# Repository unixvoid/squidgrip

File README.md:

# Squidgrip

Squidgrip is a clamp-on USB-UART probe for programming ESP32 boards. It is a CP2102N on a small
USB-C board with a 6-pin pogo pin array on a thin tongue, plus a 3D printed clamp that presses that
tongue onto the programming pads of a target board.

It carries the ESP32 auto-reset circuit, so esptool, the ExpressLRS Configurator, PlatformIO, Arduino
IDE, etc can drop a target into the bootloader and flash it without you touching anything. There
are RESET and BOOT buttons for doing it by hand, power/TX/RX LEDs, and a 3.3 V LDO so the probe can
power the board it is flashing.

<p align="center">
  
  <br>
  <em>squidgrip in the clamp (3D render)</em>
  <br><br>

  <br>
  <em>Copper and silkscreen: front and rear</em>
  <br><br>

  <br>
  <em>Assembled: front, side and rear</em>
  <br><br>

  <br>
  <em>Bare PCB front and rear, and the CAD assembly</em>
</p>

## Contents

- [Features](#features)
- [Specs](#specs)
- [How it works](#how-it-works)
- [Pinout](#pinout)
- [Configuring the CP2102N](#configuring-the-cp2102n)
- [Using it](#using-it)
- [The clamp](#the-clamp)
- [Bill of materials](#bill-of-materials)
- [Manufacturing](#manufacturing)
- [Repo layout](#repo-layout)
- [License](#license)

## Features

- CP2102N USB-UART bridge on USB-C. It shows up as a normal serial port, no drivers needed on
  Windows 10 or newer, macOS and Linux.
- The one-time CP2102N configuration is in `firmware/`, so a clone comes up with a proper name
  instead of as a generic bridge.
- ESP32 auto-reset circuit (a dual transistor driven by DTR and RTS), so flashing tools can put the
  target into the bootloader on their own.
- RESET and BOOT buttons for manual control.
- Power, TX and RX LEDs.
- 6-pin pogo array on a thin tongue, 2x3 at 1.27 mm pitch, so you can reach a small pad
  array on a crowded board. Or get a 90 degree header for even tighter access.
- 3.3 V LDO on board: the probe can power the target while flashing, no second supply needed.
- 3D printed clamp (upper jaw, lower jaw, pivot pin) that holds the pogo pins on the target pads.
- 42.75 x 19.00 mm, 2 layers, 1.6 mm FR-4.
## Specs

| Item | Value |
| --- | --- |
| USB | USB-C receptacle (Molex 2171790001), USB 2.0 only, 5.1 kΩ CC pulldowns |
| USB-UART bridge | Silicon Labs CP2102N-A02-GQFN24 (QFN-24) |
| Regulator | TLV75733, 3.3 V out from USB 5 V |
| Programming pins | 6 pogo pins on a 2x3 array at 1.27 mm pitch (Mill-Max 855-22-006-30-001101) |
| Auto reset | MBT3904DW1T1G dual NPN plus two 10 kΩ resistors, driven by DTR and RTS |
| Buttons | RESET (SW1) and BOOT (SW2), C&K PTS526 SM15 SMTR2 LFS |
| LEDs | PWR (blue), TX (yellow), RX (green) |
| Board | 42.75 x 19.00 mm, 2 layers, 1.51 mm FR-4 core, 1 oz copper, about 1.6 mm total |
| Mounting | 2 x M2 holes plus the 3D printed clamp |
| Clamp parts | `clamp_upper.step`, `clamp_lower.step`, `pin.step` |

## How it works

```
   USB-C ─────▶ +5V ─────▶ TLV75733 ─────▶ +3.3V ─────▶ pogo VCC (powers the target)
     │                        (3.3 V LDO)
     │ D+ / D-
     ▼
  CP2102N ── TXD ──▶ pogo RX   (target RXD0)
     │    ── RXD ◀── pogo TX   (target TXD0)
     │
     │ DTR / RTS
     ▼
  MBT3904 (dual NPN) ──▶ pogo RST/EN (target EN) and pogo BOOT (target IO0)

  SW1 = RESET, SW2 = BOOT, D1/D2/D3 = PWR/TX/RX LEDs
```

The auto-reset part is the standard ESP32 arrangement: DTR and RTS from the CP2102N drive two
transistors through 10 kΩ resistors, which pull EN low and hold IO0 low in the right order. That is
the same trick an ESP32 dev board uses, so esptool and friends can reset the target into the
bootloader by themselves. The buttons do the same job by hand if you need them.

The CP2102N runs off the 3.3 V rail (VREGIN, VDD and VIO are all tied to +3.3 V), senses USB VBUS on
+5 V, and has a 1 kΩ pull-up on its reset pin.

Main connections on U1:

| U1 pin | Name | Net |
| --- | --- | --- |
| 3, 4 | D+, D- | USB data from J1 |
| 8 | VBUS | +5V |
| 5, 6, 7 | VIO, VDD, VREGIN | +3.3V |
| 9 | ~RST | R5 1 kΩ pull-up to +3.3V |
| 20, 21 | RXD, TXD | pogo TX (pad 5), pogo RX (pad 6) |
| 19, 23 | ~RTS, ~DTR | auto-reset transistors (U2) |
| 13, 14 | ~TXT, ~RXT | RX and TX LED cathodes |
| 2, 25 | GND | GND |

## Pinout

Six pins, 2x3 array at 1.27 mm pitch. One column is GND / RST-EN / VCC and the other is
RX / TX / BOOT, and the silkscreen labels match the layout. TX and RX are named from the *target's*
point of view, so the pin marked RX is the one the probe drives and the pin marked TX is the one the
probe reads.

| Silk | Pad | Net | Probe side | Target side |
| --- | --- | --- | --- | --- |
| GND | 1 | `GND` | ground | ground |
| RST/EN | 2 | `/RESET` | auto-reset transistor, SW1 | EN (reset) |
| VCC | 3 | `+3.3V` | 3.3 V from the LDO | 3V3 |
| BOOT | 4 | `/BOOT` | auto-reset transistor, SW2 | IO0 (boot select) |
| TX | 5 | `/RXD` | CP2102N RXD (input) | target TXD0 |
| RX | 6 | `/TXD` | CP2102N TXD (output) | target RXD0 |

To put it on your own board: 6 pads, 1 mm diameter, 0.54 mm holes, 1.27 mm pitch, in a 2x3 block with
that pinout. It is in this repo as `hardware/squidgrip_pogo_2x03_P1.27mm.kicad_mod`, and the
[SquidTX Nano](https://github.com/unixvoid/SquidTX-Nano-ELRS) TX board carries it as SG1, so the two
work together out of the box.
## Configuring the CP2102N

The CP2102N leaves the factory with a generic identity, so it needs a one-time configuration before
the probe behaves like a squidgrip. That configuration is in `firmware/`, and Silicon Labs' own tool
programs it.

**Tool:** [Simplicity Studio](https://www.silabs.com/developers/simplicity-studio) with the
**Xpress Configurator**. The `firmware/` folder is a Simplicity Studio project, and its settings file
pins the exact part (`ffd.usbxpress.cp2102n.cp2102n_a02_gqfn24`).

| File | What it is |
| --- | --- |
| `firmware/.project`, `firmware/.settings/` | Simplicity Studio project metadata, so the folder opens straight in the IDE |
| `firmware/squidgrip.document` | the device configuration document |
| `firmware/squidgrip.configuration` | the saved configuration: `FilterVidPid` 10C4:EA60 plus the config byte array |

Steps:

1. Install Simplicity Studio, then plug the squidgrip into USB-C.
2. Open the `firmware/` project, or make a new Xpress Configurator project and open its document file.
3. Use **Import From Device** to read the chip's current configuration, then set the fields you want.
   The one that matters is the **Product String**, because that is the name your OS shows for the
   port (set it to `squidgrip`). The manufacturer string and serial number are also there.
4. Click **Program to Device**.
5. Unplug and replug the probe. It comes up under the new name.

The configuration keeps Silicon Labs' VID/PID (10C4:EA60) instead of a custom one, and that is
deliberate: the stock VCP driver matches it, so there are no `.inf` edits and no driver install. If
you change the VID/PID you are on your own for driver matching.

Two notes from Silicon Labs' documentation. If Simplicity Studio does not pick up the new name after
programming, clear its device cache: delete the device's `.info` file from
`SimplicityStudio/<workspace>/.metadata/.plugins/com.silabs.ss.platform.device.core/device` and
replug. And if the product string in `squidgrip.configuration` is still Silicon Labs' default
(`CP2102N USB to UART Bridge Controller`), then that is the field to change in step 3.

## Using it

1. Plug the squidgrip into USB. The blue PWR LED lights up and a serial port appears. The CP2102N
   needs no drivers on Windows 10 or newer, macOS and Linux.
2. Line the tongue up with the pad array on the target board and close the clamp. The pogo pins point
   down from the underside of the tongue, so the target sits below it.
3. Flash. The auto-reset circuit does the reset and boot pin dance for you, so anything that talks to
   a serial port works: the ExpressLRS Configurator (pick the target, set the upload method to UART,
   choose the COM port, Build & Flash), PlatformIO, the Arduino IDE, or plain esptool, for example:

   ```
   esptool.py --chip esp32 --port COM5 --baud 921600 write_flash 0x0 firmware.bin
   ```

The TX and RX LEDs blink with traffic, so you can see whether the target is answering. If a tool
cannot get the target into the bootloader, do it by hand: hold BOOT, tap RESET, release BOOT.

Two things worth knowing:

- The probe feeds 3.3 V to the target through the VCC pin, so a bare board can be flashed with
  nothing else connected. If the target already has its own supply, be aware the two will be tied
  together.
- The 3.3 V rail comes from the TLV75733 and USB VBUS, so what you can pull depends on the USB port
  you are plugged into. It is plenty for an ESP32 (and an RF module while flashing).

## The clamp

It works like an alligator clip. Three printed parts in `hardware/clamp_design/`:

| File | Part | Qty |
| --- | --- | --- |
| `squidgrip - clamp_upper.step` | upper jaw (SQUIDGRIP embossed on it) | 1 |
| `squidgrip - clamp_lower.step` | lower jaw | 1 |
| `squidgrip - pin.step` | pins that connect the PCB to the print | 2 |

Hardware:

| Part | McMaster-Carr | Qty |
| --- | --- | --- |
| M3 x 16 mm socket head cap screw | 91292A115 | 1 |
| M3 nyloc nut | 93625A100 | 1 |
| Spring (in the handle) | 9271K577 | 2 |

The two printed pins hold the PCB to the clamp, the M3 screw and nyloc nut are the pivot, and the two
springs sit in the handle so the jaws spring back open. The target board goes between the jaws, under
the tongue. The one in the photos is FDM printed, so print settings are up to you. `squidgrip.step`
in `hardware/manufacturing/` is the finished assembly if you want to check clearances before
printing.

## Bill of materials

Parts that LCSC can assemble (this is the CSV in `hardware/manufacturing/`):

| Ref | Value / Part | Package | LCSC |
| --- | --- | --- | --- |
| U1 | CP2102N-A02-GQFN24R | QFN-24 4x4 | C969151 |
| U2 | MBT3904DW1T1G | SOT-363 | C110150 |
| U3 | TLV75733PDRVR | WSON-6 2x2 | C2868428 |
| C1 | 4.7 µF | 0805 | C1779 |
| C2, C3 | 0.1 µF | 0805 | C1711 |
| R1, R8 | 10 kΩ | 0805 | C17414 |
| R5 | 1 kΩ | 0805 | C17513 |
| R6, R7 | 5.1 kΩ | 0805 | C27834 |
| R9, R10, R11 | 2.2 kΩ | 0805 | C17520 |

Everything else is hand soldered:

| Ref | Part | Notes |
| --- | --- | --- |
| J1 | Molex 2171790001 | USB-C receptacle |
| SG1 | Mill-Max 855-22-006-30-001101 | 6-position pogo pin header |
| SW1, SW2 | C&K PTS526 SM15 SMTR2 LFS | RESET and BOOT switches |
| D1, D2, D3 | 0805 LEDs, yellow / green / blue | TX, RX, PWR |
| - | 2 x M2 screws | PCB to clamp |
| - | pivot pin or screw for the hinge | see `hardware/clamp_design/` |
## Manufacturing

| File | Description |
| --- | --- |
| `hardware/squidgrip.kicad_pro` | KiCad project (design rules and netclass) |
| `hardware/squidgrip.kicad_sch` | schematic (title block: Squidgrip ESP32 Interface, rev 1.4, Midnight CAD) |
| `hardware/squidgrip.kicad_pcb` | PCB layout |
| `hardware/manufacturing/squidgrip-v1.4-gerbers.zip` | gerber and drill package, ready to upload |
| `hardware/manufacturing/gerbers/` | the same files unpacked (F and B Cu, mask, paste, silk, Edge_Cuts, PTH and NPTH drills, job) |
| `hardware/manufacturing/squidgrip_v1.4_BOM.csv` | BOM with LCSC part numbers, in the JLCPCB assembly format |
| `hardware/manufacturing/squidgrip.step` | 3D model of the assembled board |
| `hardware/clamp_design/` | clamp STEP files |
| `hardware/squidgrip_pogo_2x03_P1.27mm.kicad_mod` | the 6-pin pogo footprint on its own, for your own boards |
| `docs/` | photos, layer renders and the CAD image used here |

Fab options that match the layout:

- 2 layers, 1.6 mm FR-4, 1 oz copper (1.51 mm core plus 2 x 0.035 mm copper).
- 0.1524 mm minimum track and clearance, 0.2 mm netclass tracks with 0.16 mm clearance, 0.6 mm vias
  with a 0.3 mm drill, 0.5 mm copper to the board edge. Those are the values in the project file.
- ENIG is worth the extra if you want the pogo pads and the USB-C shell to hold up.
- The USB-C receptacle, pogo header, switches and LEDs are hand soldered, so order those yourself
  along with the LCSC parts.

## Repo layout

```
.
├── README.md
├── LICENSE                      # CERN-OHL-S-2.0
├── docs/
│   ├── squidgrip.gif                    # 3D render of the assembly
│   ├── squidgrip_assembled_front.jpg    # photo, assembled front
│   ├── squidgrip_assembled_side.jpg     # photo, side view in the clamp
│   ├── squidgrip_assembled_rear.jpg     # photo, assembled rear
│   ├── squidgrip_pcb_front.jpg          # photo, bare PCB front
│   ├── squidgrip_pcb_rear.jpg           # photo, bare PCB rear
│   ├── squidgrip_assembly_cad.png       # CAD view of the assembly
│   ├── squidgrip_copper_front.png       # KiCad render, front copper and silk
│   └── squidgrip_copper_rear.png        # KiCad render, rear copper and silk
├── firmware/
│   ├── squidgrip.configuration          # CP2102N configuration
│   ├── squidgrip.document               # Xpress Configurator device document
│   ├── .project                         # Simplicity Studio project
│   └── .settings/                       # Simplicity Studio tool settings
└── hardware/
    ├── squidgrip.kicad_pro      # KiCad project
    ├── squidgrip.kicad_sch      # schematic
    ├── squidgrip.kicad_pcb      # PCB layout
    ├── squidgrip_pogo_2x03_P1.27mm.kicad_mod   # the 6-pin pogo footprint
    ├── clamp_design/
    │   ├── squidgrip - clamp_upper.step
    │   ├── squidgrip - clamp_lower.step
    │   └── squidgrip - pin.step
    └── manufacturing/
        ├── squidgrip-v1.4-gerbers.zip
        ├── squidgrip.step
        ├── squidgrip_v1.4_BOM.csv
        └── gerbers/             # unpacked gerbers and drill files
```

## License

squidgrip is licensed under the CERN Open Hardware Licence Version 2 - Strongly Reciprocal
(CERN-OHL-S-2.0). The full licence text is in [`LICENSE`](LICENSE).

```
Copyright (C) 2026 Midnight CAD / SquidTX

This source describes Open Hardware and is licensed under the CERN-OHL-S v2.

You may redistribute and modify this source and make products using it under
the terms of the CERN-OHL-S v2 (https://ohwr.org/cern_ohl_s_v2.txt).

This source is distributed WITHOUT ANY EXPRESS OR IMPLIED WARRANTY, INCLUDING
OF MERCHANTABILITY, SATISFACTORY QUALITY AND FITNESS FOR A PARTICULAR PURPOSE.
Please see the CERN-OHL-S v2 for applicable conditions.

Source location: https://github.com/unixvoid/squidgrip
```

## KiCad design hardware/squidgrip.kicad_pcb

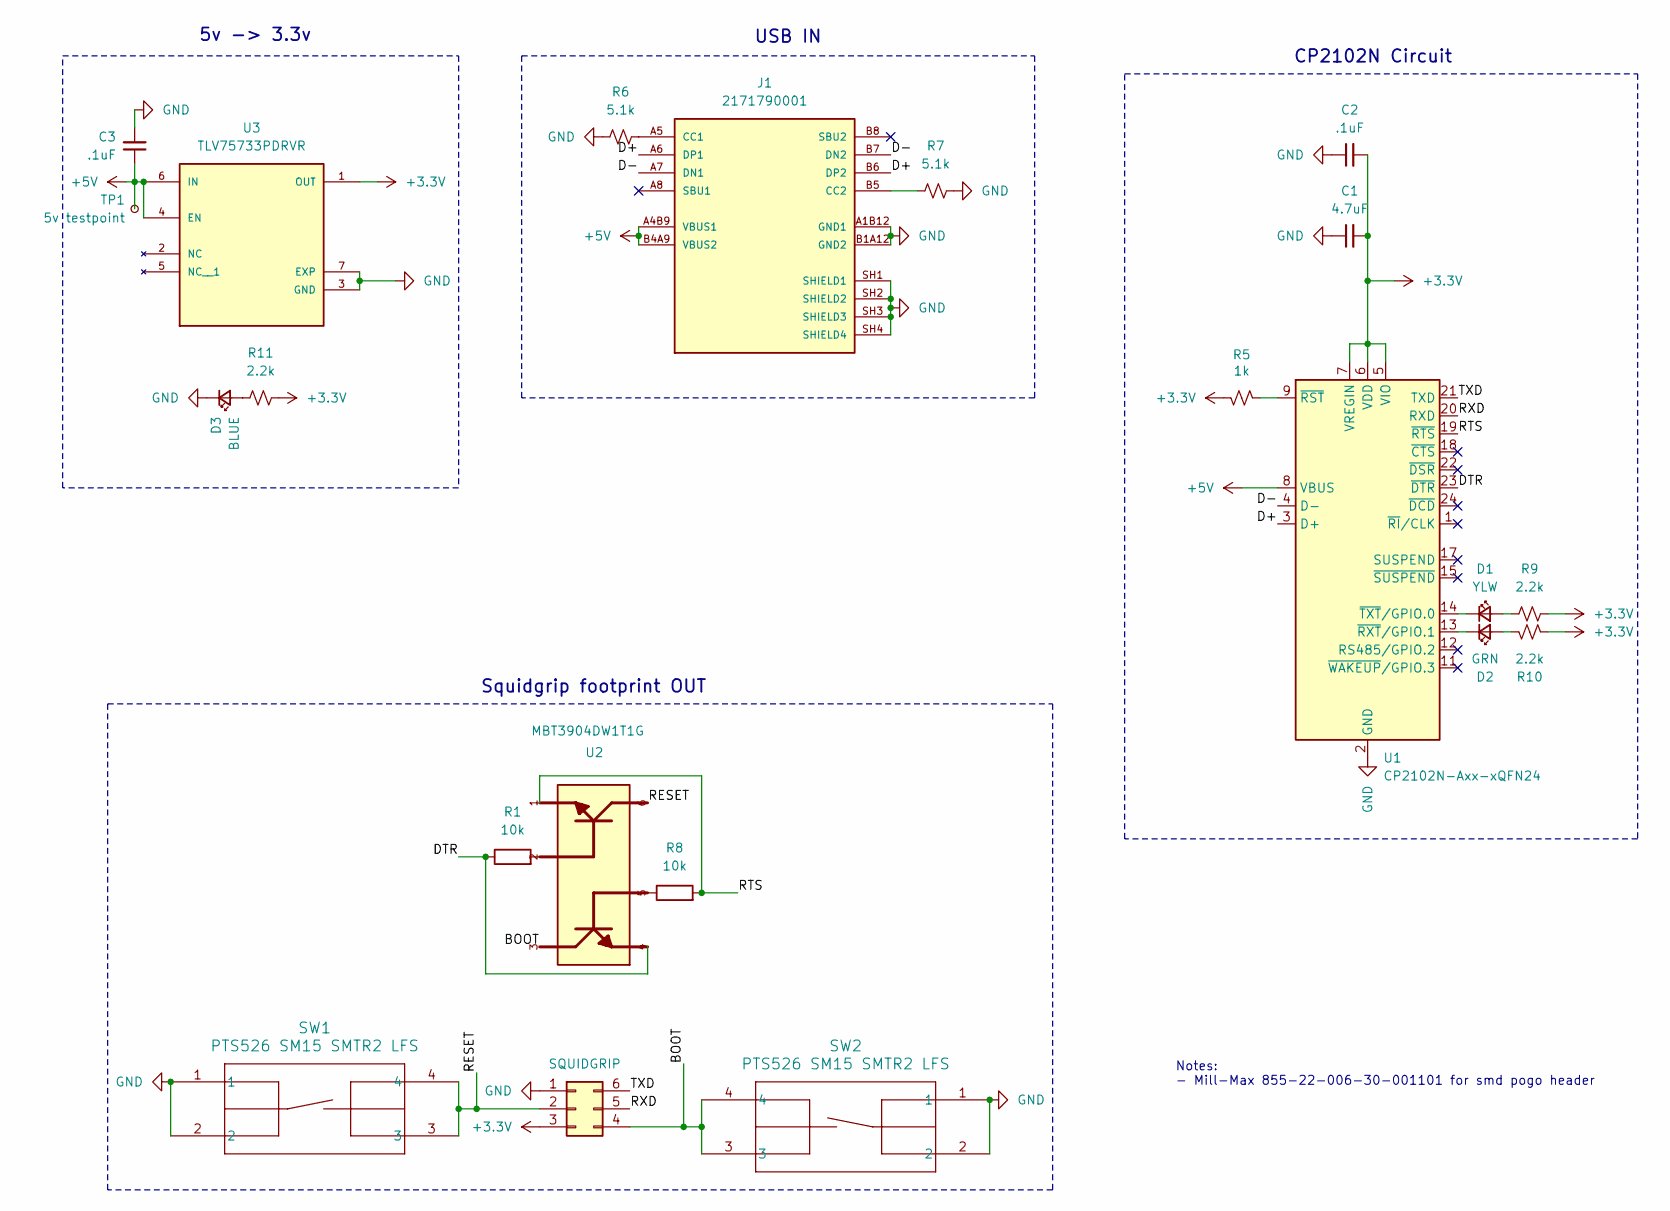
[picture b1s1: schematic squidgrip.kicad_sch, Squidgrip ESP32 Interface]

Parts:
C1: 4.7uF; C_0805_2012Metric
C2, C3: .1uF; C_0805_2012Metric
D1: YLW; LED_0805_2012Metric
D2: GRN; LED_0805_2012Metric
D3: BLUE; LED_0805_2012Metric
J1: 2171790001; MOLEX_2171790001; PARTREV A1
R1, R8: 10k; R_0805_2012Metric
R5: 1k; R_0805_2012Metric
R6, R7: 5.1k; R_0805_2012Metric
R9, R10, R11: 2.2k; R_0805_2012Metric
SG1: SQUIDGRIP; Untitled
SW1, SW2: PTS526 SM15 SMTR2 LFS; GSPTS004901
TP1: 5v testpoint; TestPoint_Pad_1.0x1.0mm
U1: CP2102N-Axx-xQFN24; QFN-24-1EP_4x4mm_P0.5mm_EP2.6x2.6mm
U2: MBT3904DW1T1G; SOT236
U3: TLV75733PDRVR

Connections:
+3.3V: C1.2, C2.2, R5.1, R9.2, R10.1, R11.2, SG1.3 (3.3v), U1.5 (VIO), U1.6 (VDD), U1.7 (VREGIN), U3.1 (OUT)
+5V: C3.1, J1.A4B9 (VBUS1), J1.B4A9 (VBUS2), TP1.1, U1.8 (VBUS), U3.4 (EN), U3.6 (IN)
/BOOT: SG1.4 (RTS), SW2.3, SW2.4, U2.3
/D+: J1.A6 (DP1), J1.B6 (DP2), U1.3 (D+)
/D-: J1.A7 (DN1), J1.B7 (DN2), U1.4 (D-)
/DTR: R1.1, U1.23 (~DTR), U2.4
/RESET: SG1.2 (DTR), SW1.3, SW1.4, U2.6
/RTS: R8.2, U1.19 (~RTS), U2.1
/RXD: SG1.5 (RXD), U1.20 (RXD)
/TXD: SG1.6 (TXD), U1.21 (TXD)
GND: C1.1, C2.1, C3.2, D3.1 (K), J1.A1B12 (GND1), J1.B1A12 (GND2), J1.SH1 (SHIELD1), J1.SH2 (SHIELD2), J1.SH3 (SHIELD3), J1.SH4 (SHIELD4), R6.1, R7.2, SG1.1 (GND), SW1.1, SW1.2, SW2.1, SW2.2, U1.2 (GND), U1.25 (GND), U3.3 (GND), U3.7 (EXP)
unnamed: D1.2 (A), R9.1
unnamed: D1.1 (K), U1.14 (~TXT/GPIO.0)
unnamed: D2.2 (A), R10.2
unnamed: D2.1 (K), U1.13 (~RXT/GPIO.1)
unnamed: D3.2 (A), R11.1
unnamed: J1.A5 (CC1), R6.2
unnamed: J1.B5 (CC2), R7.1
unnamed: R1.2, U2.2
unnamed: R8.1, U2.5
unnamed: R5.2, U1.9 (~RST)

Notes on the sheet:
5v -> 3.3v
USB IN
CP2102N Circuit
Notes: - Mill-Max 855-22-006-30-001101 for smd pogo header
Squidgrip footprint OUT

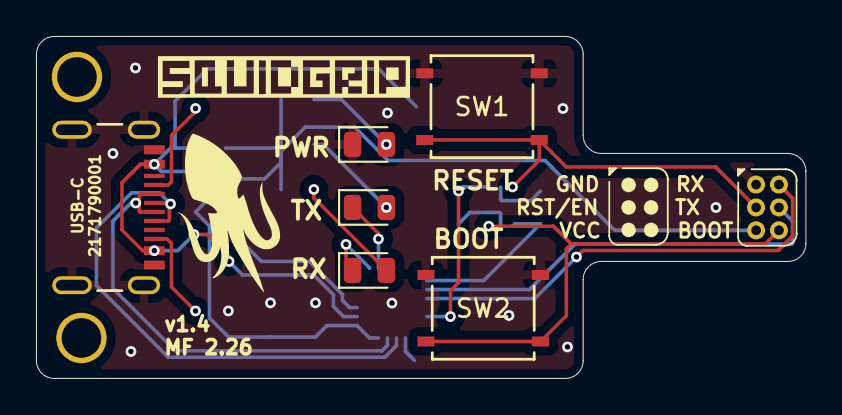
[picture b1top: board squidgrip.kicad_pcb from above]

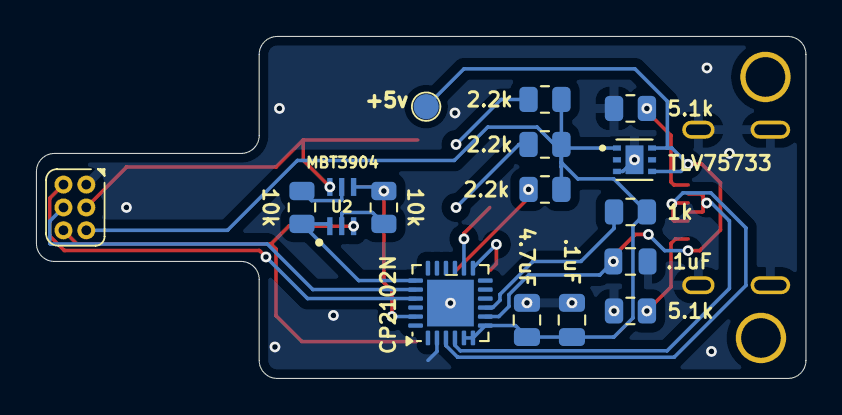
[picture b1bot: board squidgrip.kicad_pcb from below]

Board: 2 copper layers, 42.8 x 19.0 mm, 22 parts (15 on the bottom side), 21 nets.

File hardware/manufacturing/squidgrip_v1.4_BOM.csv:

Comment,Designator,Footprint,LCSC Part Number
4.7uF,C1,0805,C1779
.1uF,"C2,C3",0805,C1711
10k,"R1,R8",0805,C17414
1k,R5,0805,C17513
5.1k,"R6,R7",0805,C27834
2.2k,"R9,R10,R11",0805,C17520
CP2102N-A02-GQFN24R,U1,QFN-24-EP(4x4),C969151
MBT3904DW1T1G,U2,SOT-363,C110150
TLV75733PDRVR,U3,WSON-6(2x2),C2868428
